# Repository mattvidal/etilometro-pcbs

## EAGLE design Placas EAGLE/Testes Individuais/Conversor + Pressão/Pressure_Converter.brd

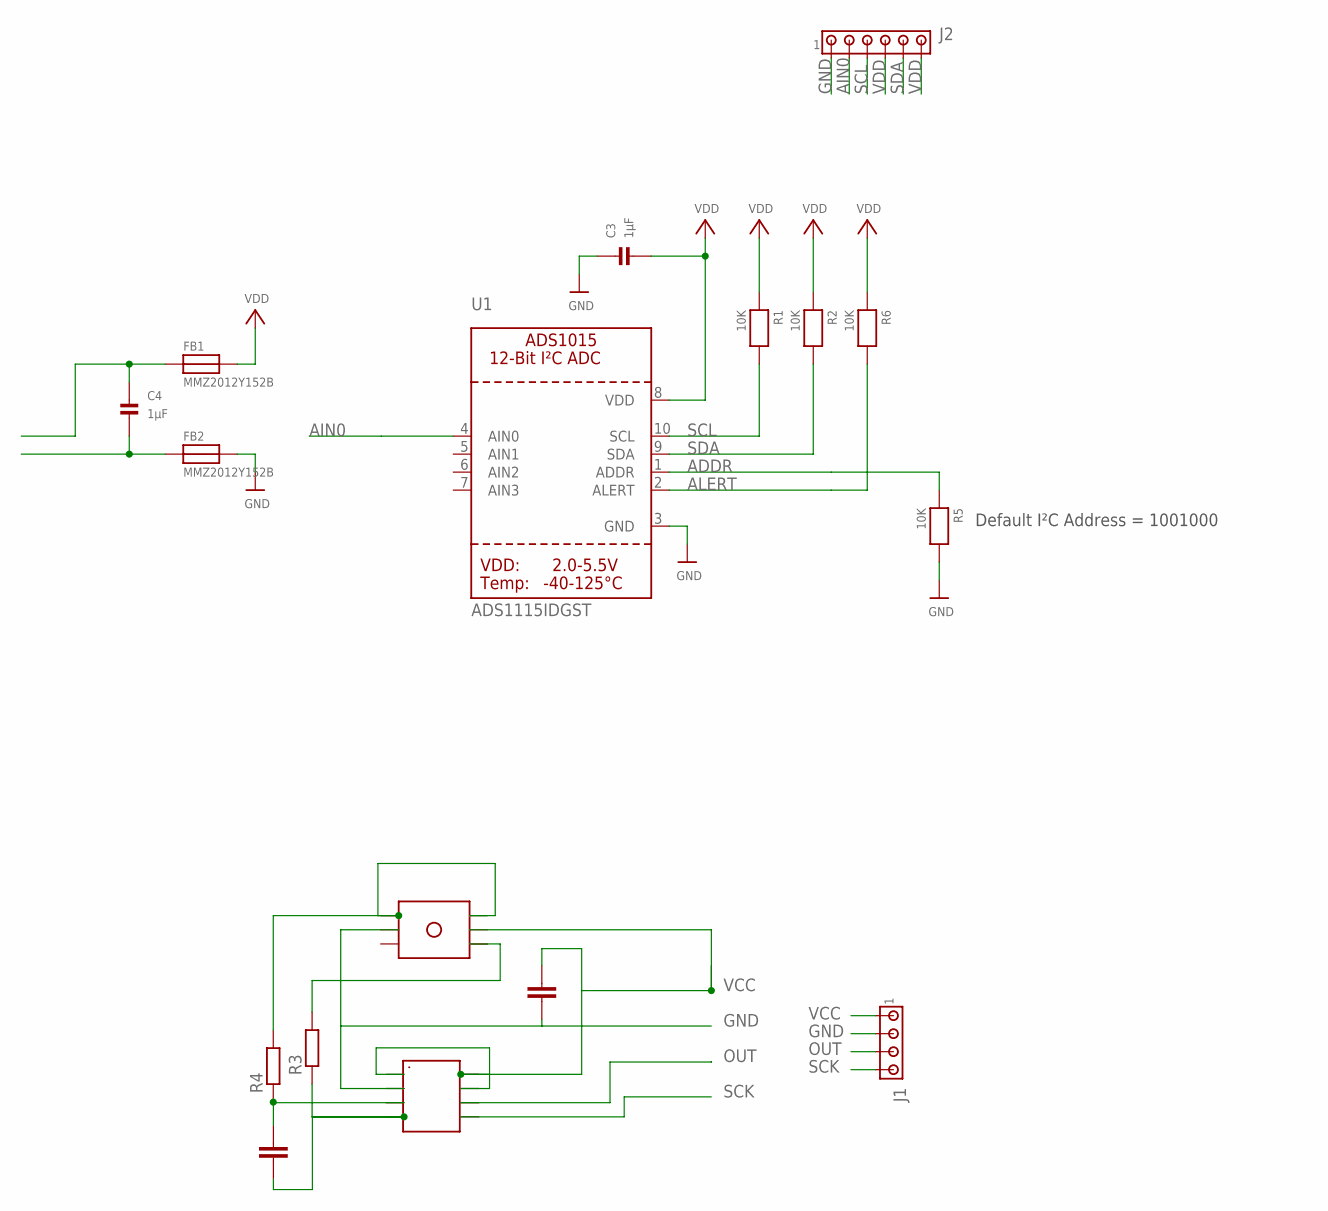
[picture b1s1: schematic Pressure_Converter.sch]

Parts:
C1, C2: 100n; C0805
C3, C4: 1µF; 0805
FB1, FB2: MMZ2012Y152B; 0805
J1: MTA04-100; 10X04MTA
J2: MTA06-156; 1X6MTA
R1, R2, R5, R6: 10K; 0805
R3, R4: R-EU_R0805; R0805
U1: ADS1115IDGST; MSOP10
U$1: HX710B
U$2: PRESSURE

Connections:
ADDR: R5.1, U1.1 (ADDR)
AIN0: J2.2, U1.4 (AIN0)
ALERT: R6.2, U1.2 (ALERT)
GND: C1.2, C3.1, FB2.2, J1.2, J2.1, R5.2, U1.3 (GND), U$1.AGND, U$2.2
unnamed: C2.2, R4.1, U$1.INN
unnamed: C2.1, R3.1, U$1.INP
unnamed: R3.2, U$2.4
unnamed: R4.2, U$2.1, U$2.6
unnamed: C4.2, FB2.1
unnamed: C4.1, FB1.1
OUT: J1.3, U$1.DOUT
SCK: J1.4, U$1.SCK
SCL: J2.3, R1.2, U1.10 (SCL)
SDA: J2.5, R2.2, U1.9 (SDA)
VCC: C1.1, J1.1, U$1.AVDD, U$1.DVDD, U$1.VREF, U$2.5
VDD: C3.2, FB1.2, J2.4, J2.6, R1.1, R2.1, R6.1, U1.8 (VDD)

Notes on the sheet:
Default I²C Address = 1001000

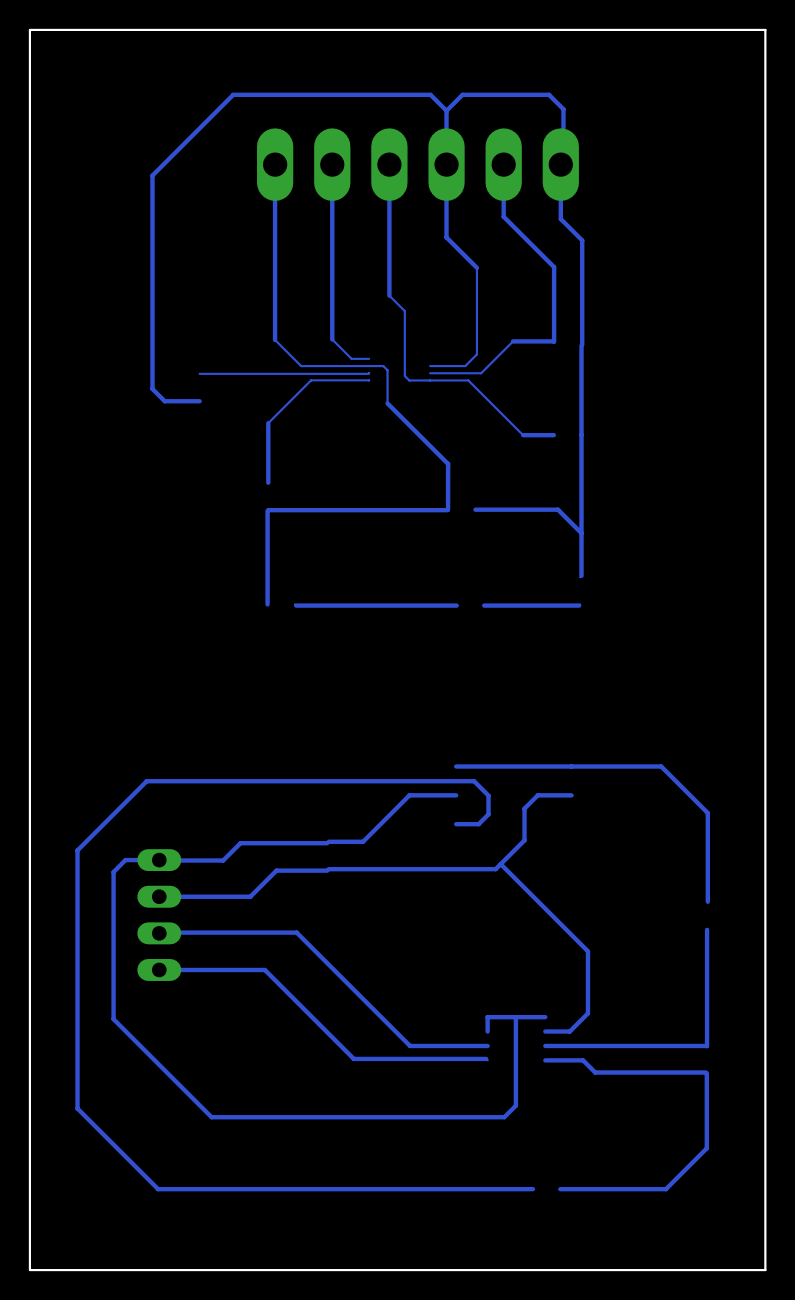
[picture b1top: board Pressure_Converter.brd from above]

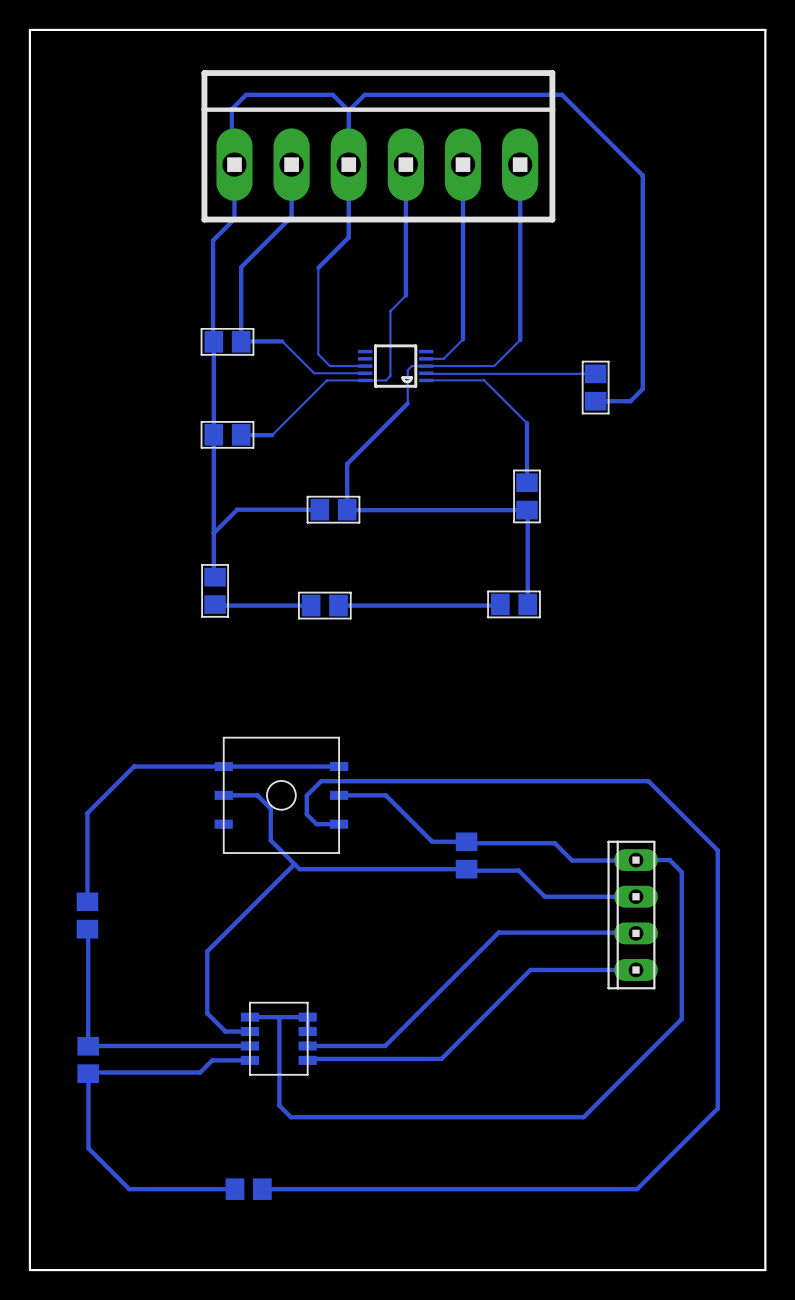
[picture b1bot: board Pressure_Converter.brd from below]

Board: 2 copper layers, 51.0 x 86.0 mm, 17 parts (17 on the bottom side), 16 nets.

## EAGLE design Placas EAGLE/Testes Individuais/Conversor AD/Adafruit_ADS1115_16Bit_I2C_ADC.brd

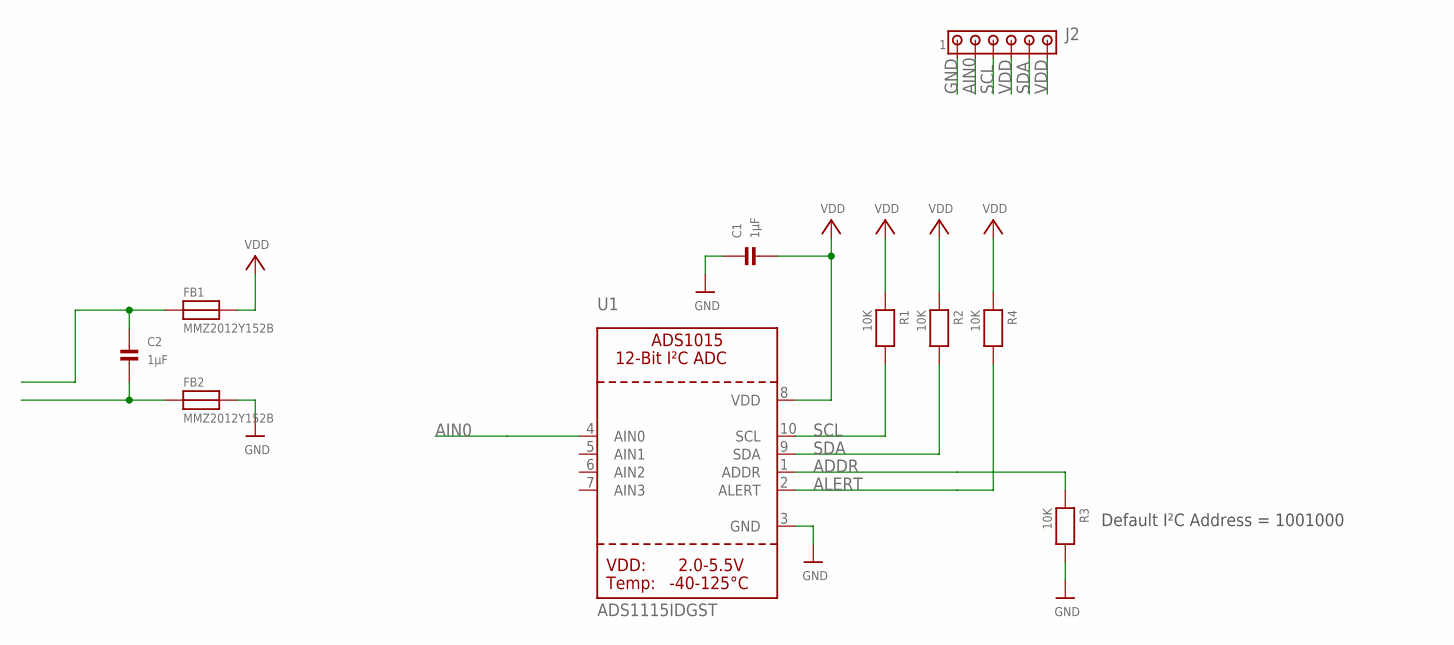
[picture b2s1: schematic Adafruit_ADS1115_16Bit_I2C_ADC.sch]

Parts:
C1, C2: 1µF; 0805
FB1, FB2: MMZ2012Y152B; 0805
J2: MTA06-156; 1X6MTA
R1, R2, R3, R4: 10K; 0805
U1: ADS1115IDGST; MSOP10

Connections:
ADDR: R3.1, U1.1 (ADDR)
AIN0: J2.2, U1.4 (AIN0)
ALERT: R4.2, U1.2 (ALERT)
GND: C1.1, FB2.2, J2.1, R3.2, U1.3 (GND)
unnamed: C2.1, FB1.1
unnamed: C2.2, FB2.1
SCL: J2.3, R1.2, U1.10 (SCL)
SDA: J2.5, R2.2, U1.9 (SDA)
VDD: C1.2, FB1.2, J2.4, J2.6, R1.1, R2.1, R4.1, U1.8 (VDD)

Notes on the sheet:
Default I²C Address = 1001000

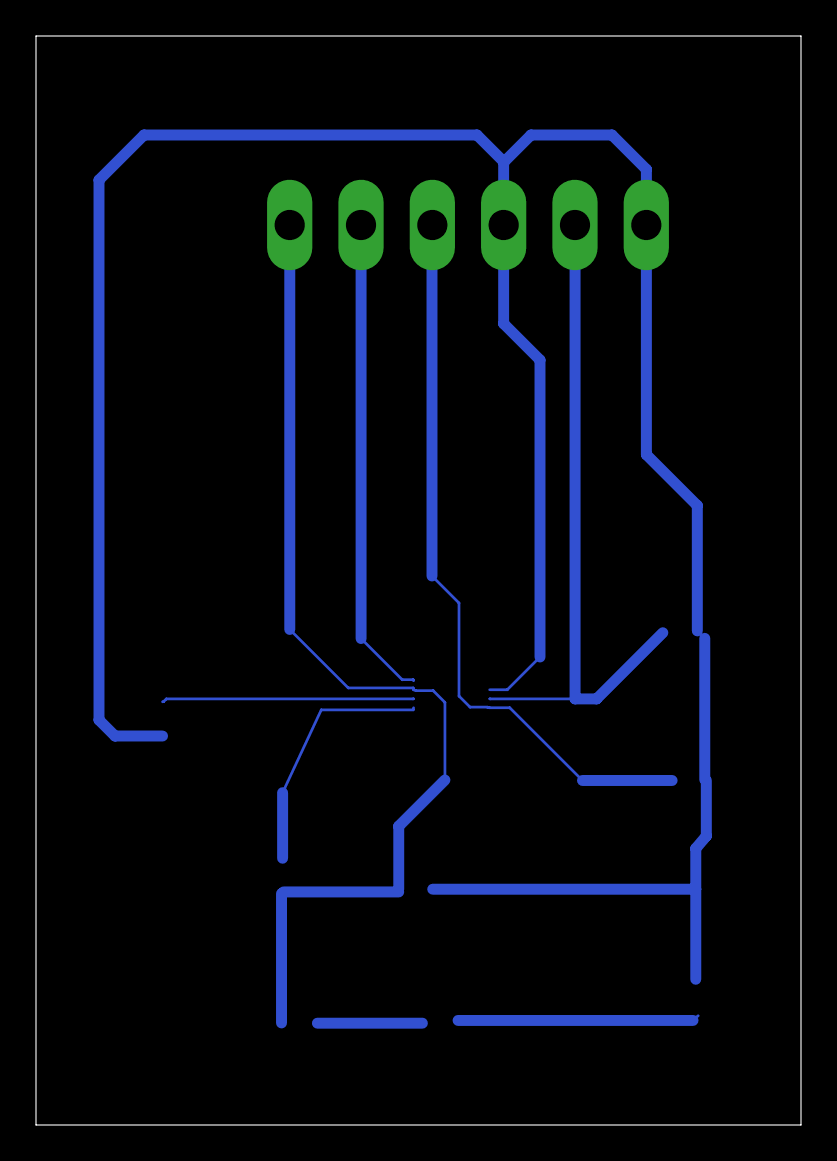
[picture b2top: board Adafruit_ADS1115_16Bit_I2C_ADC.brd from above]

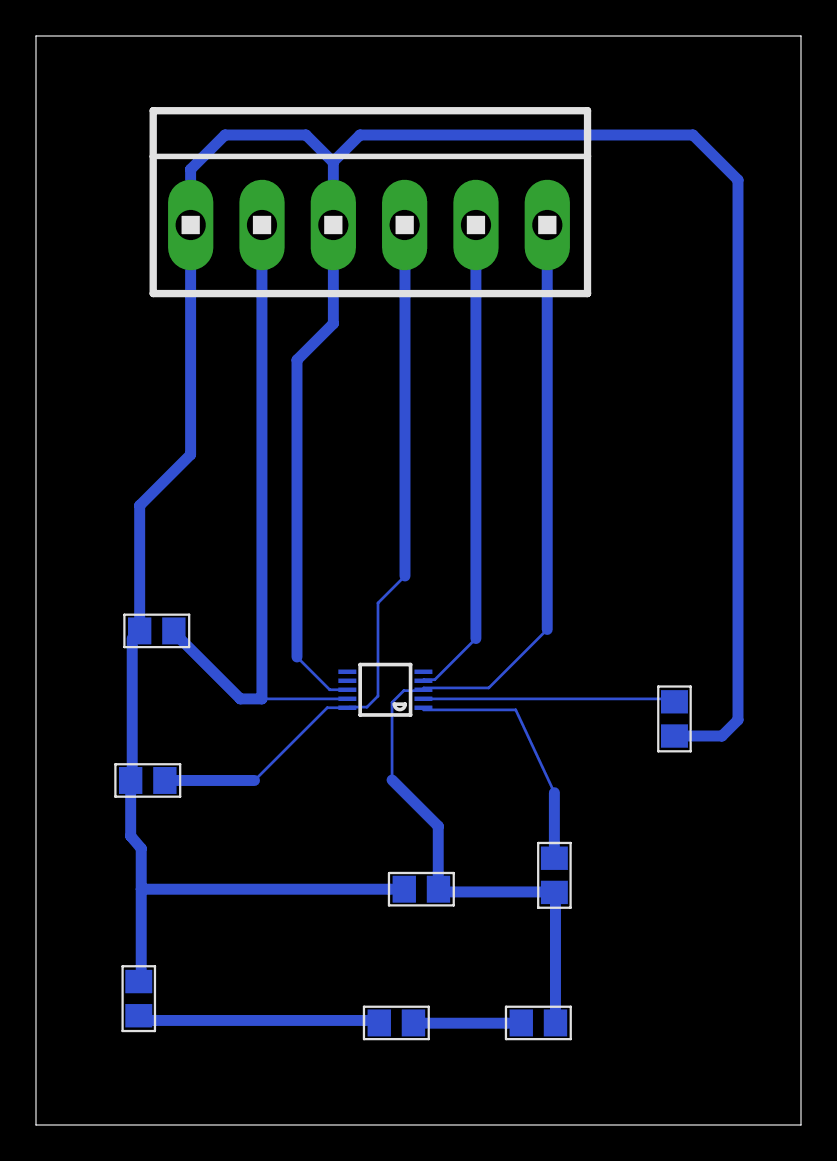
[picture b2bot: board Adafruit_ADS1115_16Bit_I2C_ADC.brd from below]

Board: 2 copper layers, 42.5 x 60.5 mm, 10 parts (10 on the bottom side), 9 nets.

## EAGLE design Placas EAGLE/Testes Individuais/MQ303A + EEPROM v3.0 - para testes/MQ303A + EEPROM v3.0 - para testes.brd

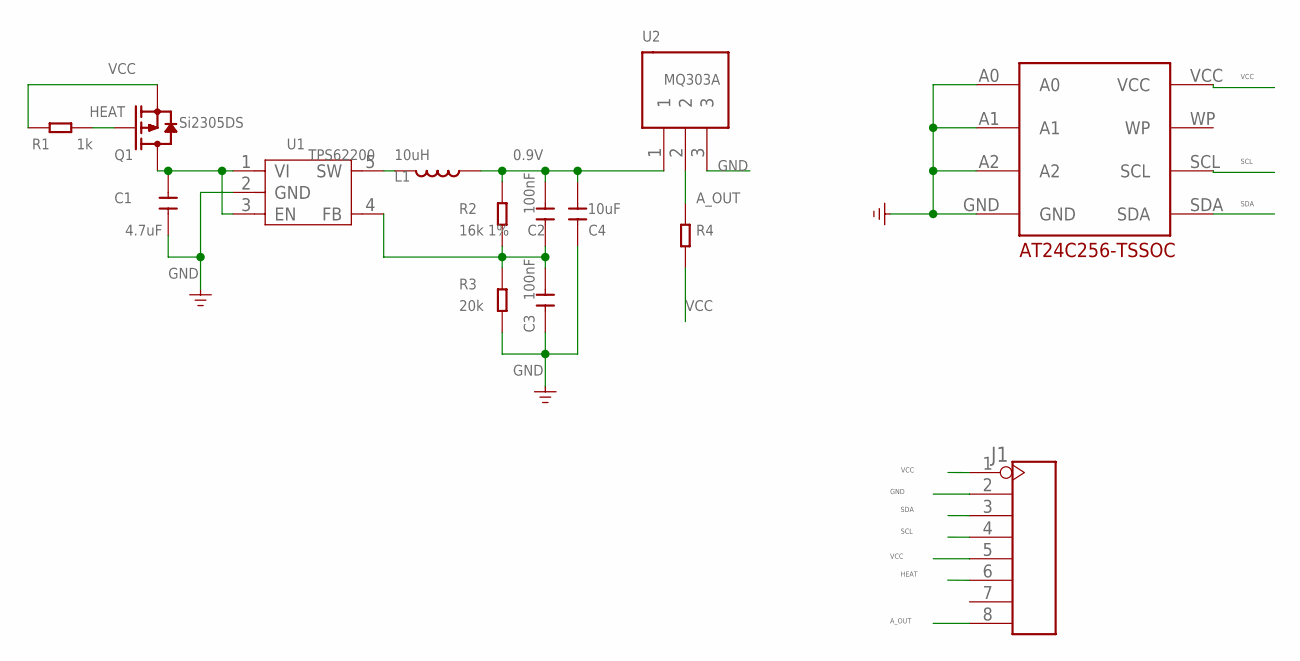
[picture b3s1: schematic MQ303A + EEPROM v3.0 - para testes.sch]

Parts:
C1: 4.7uF; C0805
C2, C3: 100nF; C0603
C4: 10uF; C0805
J1: HEADER-8P-2.54; 8P-2.54
L1: 10uH; PIO73
Q1: Si2305DS; SOT23
R1: 1k; R0603
R2: 16k 1%; R0603
R3: 20k; R0603
R4: R-0603; R0603
U1: TPS62200; SOT23-5
U2: MQ303A
U$1: DECADE-AT24C256-10TI-2.7; DECADE-AT24CXX

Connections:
0.9V: C2.2, C4.2, L1.2, R2.1, U2.1
A_OUT: J1.8, R4.1, U2.2
GND: C1.2, C3.1, C4.1, J1.2, R3.2, U1.2 (GND), U2.3, U$1.A0, U$1.A1, U$1.A2, U$1.GND
HEAT: J1.6, Q1.1 (G), R1.1
unnamed: C1.1, Q1.3 (D), U1.1 (VI), U1.3 (EN)
unnamed: L1.1, U1.5 (SW)
unnamed: C2.1, C3.2, R2.2, R3.1, U1.4 (FB)
SCL: J1.4, U$1.SCL
SDA: J1.3, U$1.SDA
VCC: J1.1, J1.5, Q1.2 (S), R1.2, R4.2, U$1.VCC

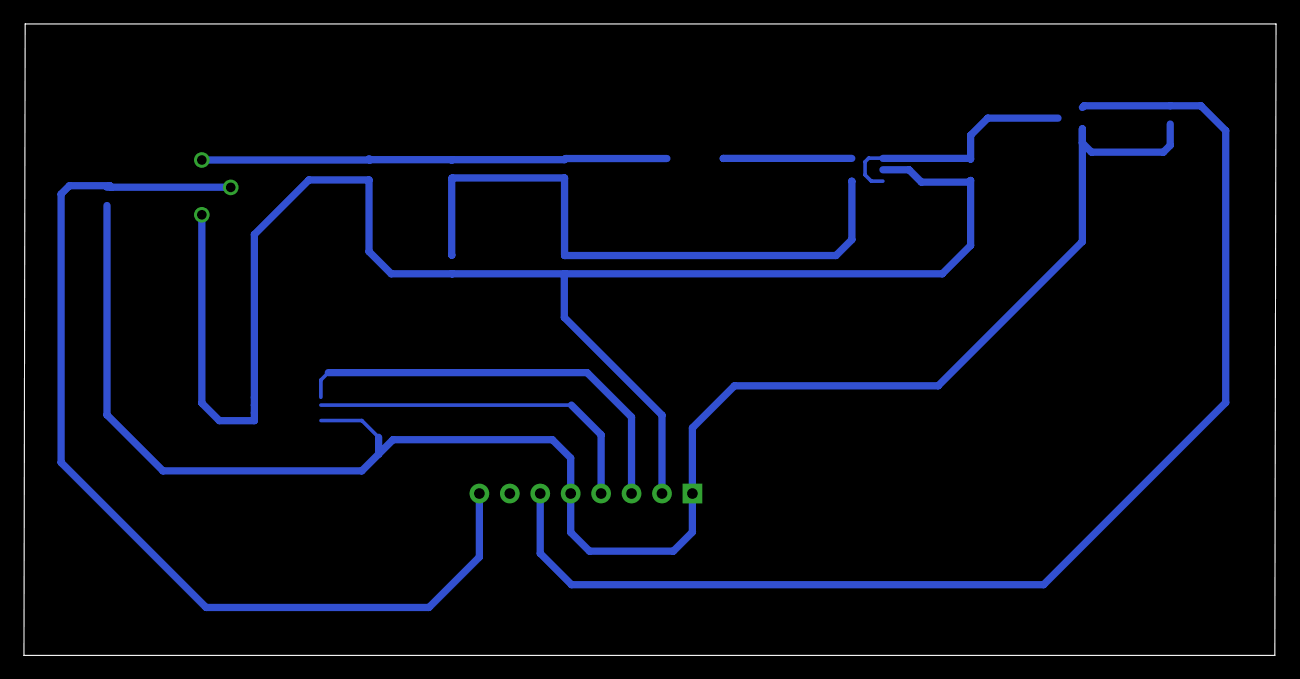
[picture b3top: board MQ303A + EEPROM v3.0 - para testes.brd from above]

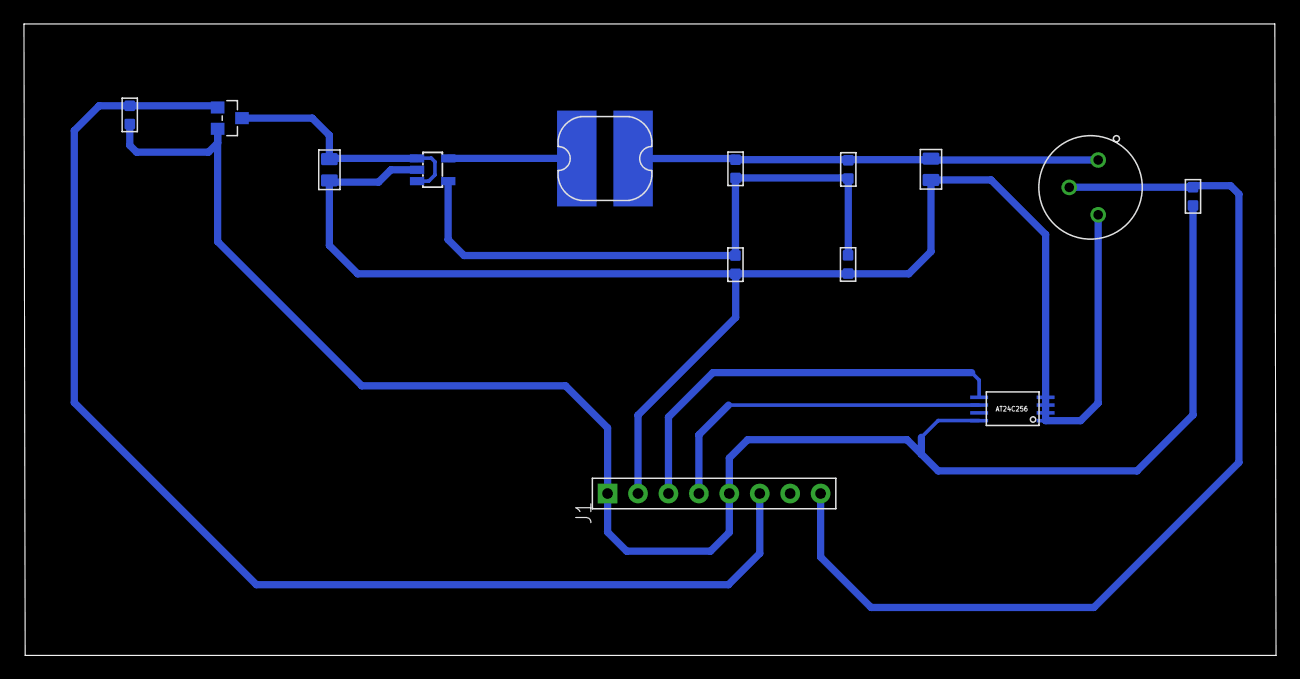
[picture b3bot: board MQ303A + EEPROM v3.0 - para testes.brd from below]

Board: 2 copper layers, 104.5 x 52.7 mm, 14 parts (14 on the bottom side), 10 nets.

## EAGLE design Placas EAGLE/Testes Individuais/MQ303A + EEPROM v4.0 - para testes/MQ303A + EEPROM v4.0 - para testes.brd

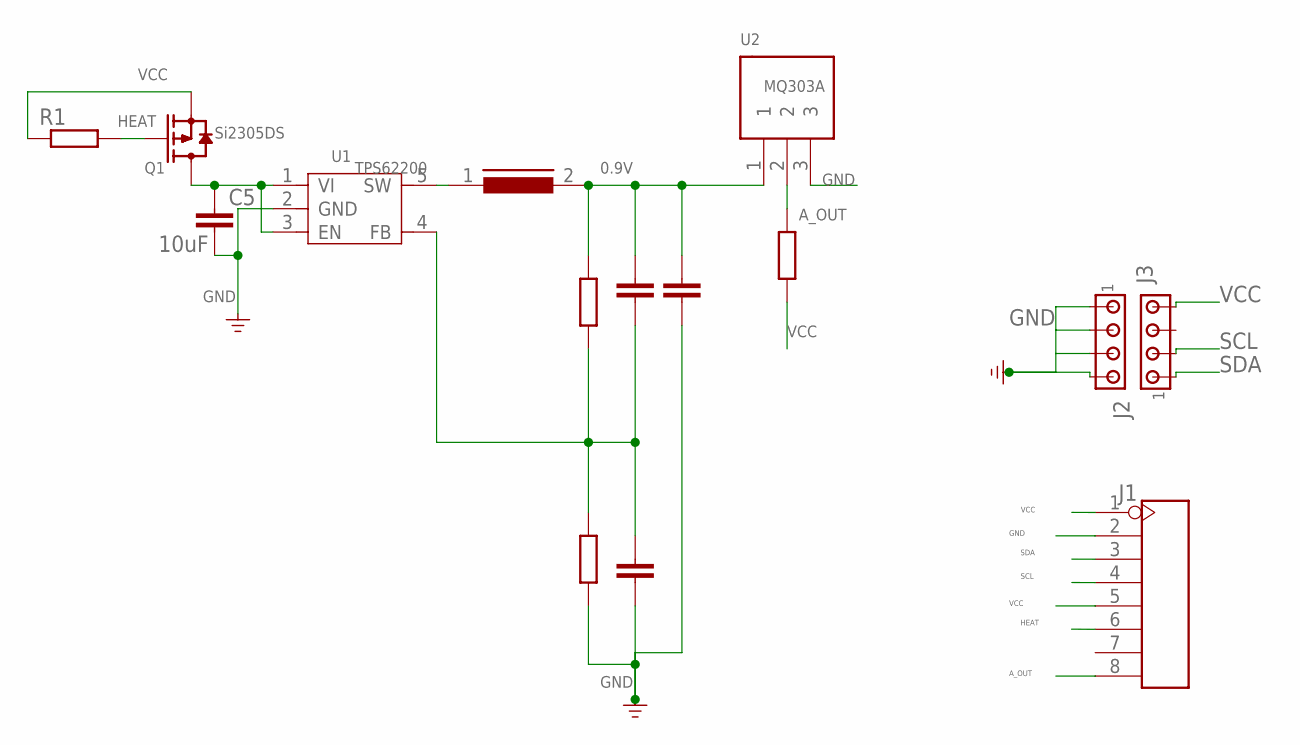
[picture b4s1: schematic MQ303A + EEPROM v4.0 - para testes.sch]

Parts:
C1, C2, C3, C5: 10uF; C050-025X075
J1: HEADER-8P-2.54; 8P-2.54
J2, J3: MTA04-100; 10X04MTA
L2: MMICC7
Q1: Si2305DS; SOT23
R1, R2, R3, R5: R-EU_0207/10; 0207/10
U1: TPS62200; SOT23-5
U2: MQ303A

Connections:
0.9V: C1.1, C3.1, L2.2, R5.2, U2.1
A_OUT: J1.8, R3.2, U2.2
GND: C2.2, C3.2, C5.2, J1.2, J2.1, J2.2, J2.3, J2.4, R2.1, U1.2 (GND), U2.3
HEAT: J1.6, Q1.1 (G), R1.2
unnamed: C5.1, Q1.3 (D), U1.1 (VI), U1.3 (EN)
unnamed: L2.1, U1.5 (SW)
unnamed: C1.2, C2.1, R2.2, R5.1, U1.4 (FB)
SCL: J1.4, J3.2
SDA: J1.3, J3.1
VCC: J1.1, J1.5, J3.4, Q1.2 (S), R1.1, R3.1

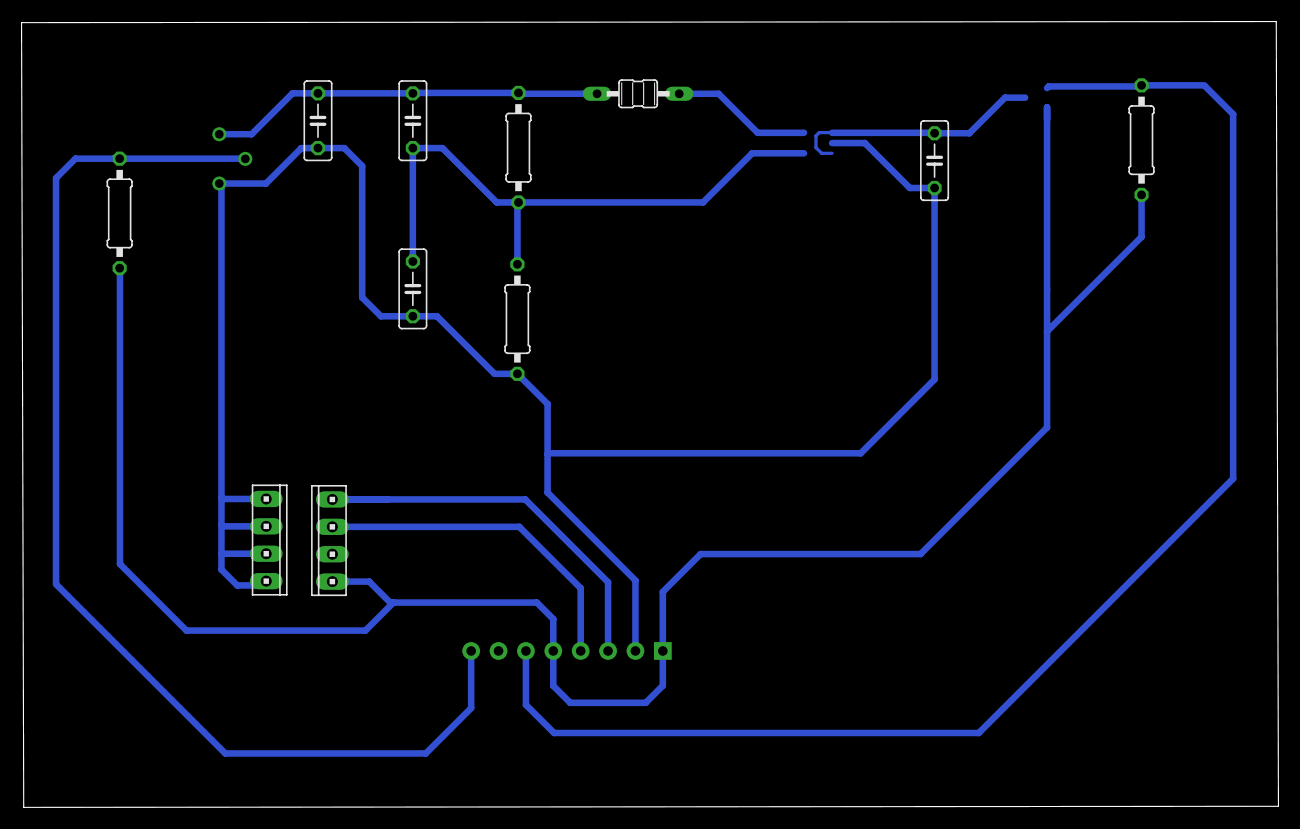
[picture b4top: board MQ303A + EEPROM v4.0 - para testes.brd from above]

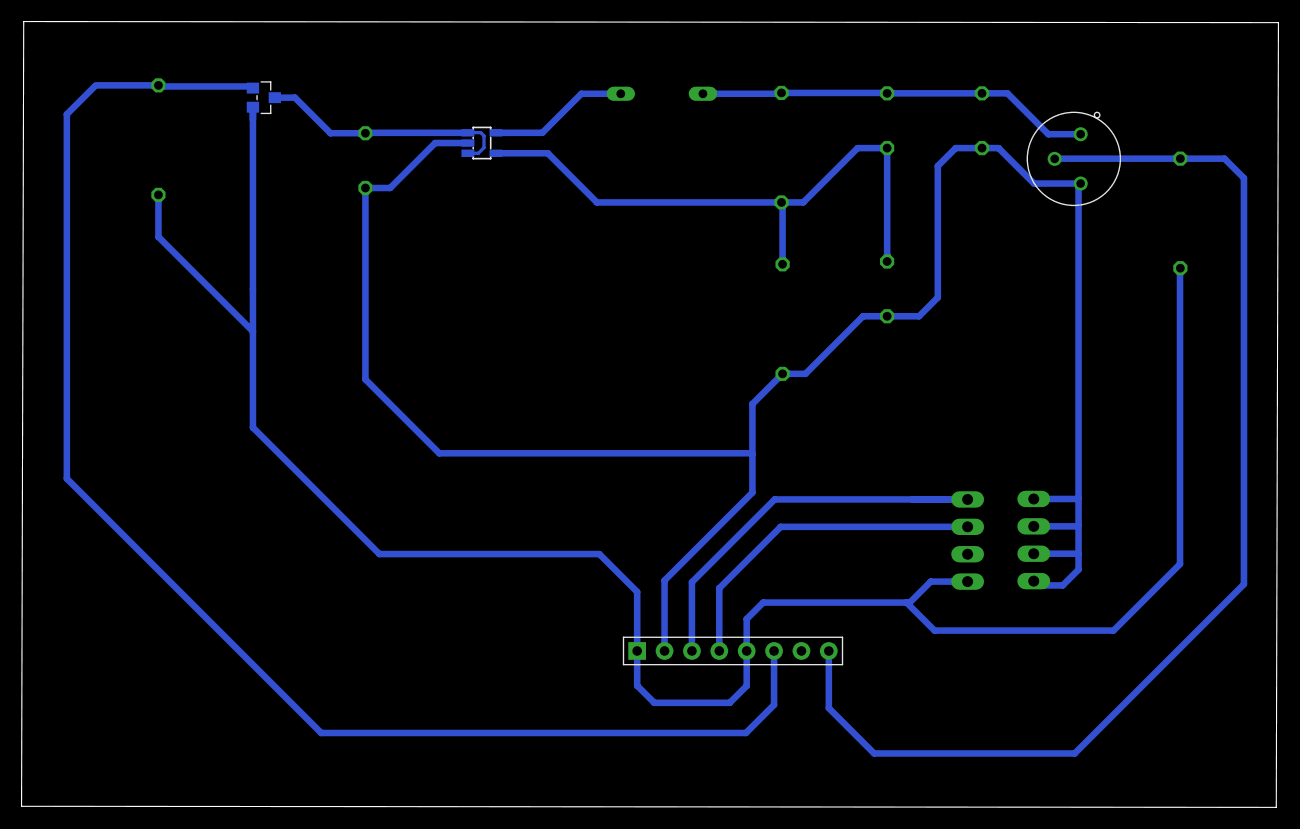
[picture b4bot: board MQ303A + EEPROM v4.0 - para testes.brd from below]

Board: 2 copper layers, 116.6 x 72.9 mm, 15 parts (4 on the bottom side), 10 nets.

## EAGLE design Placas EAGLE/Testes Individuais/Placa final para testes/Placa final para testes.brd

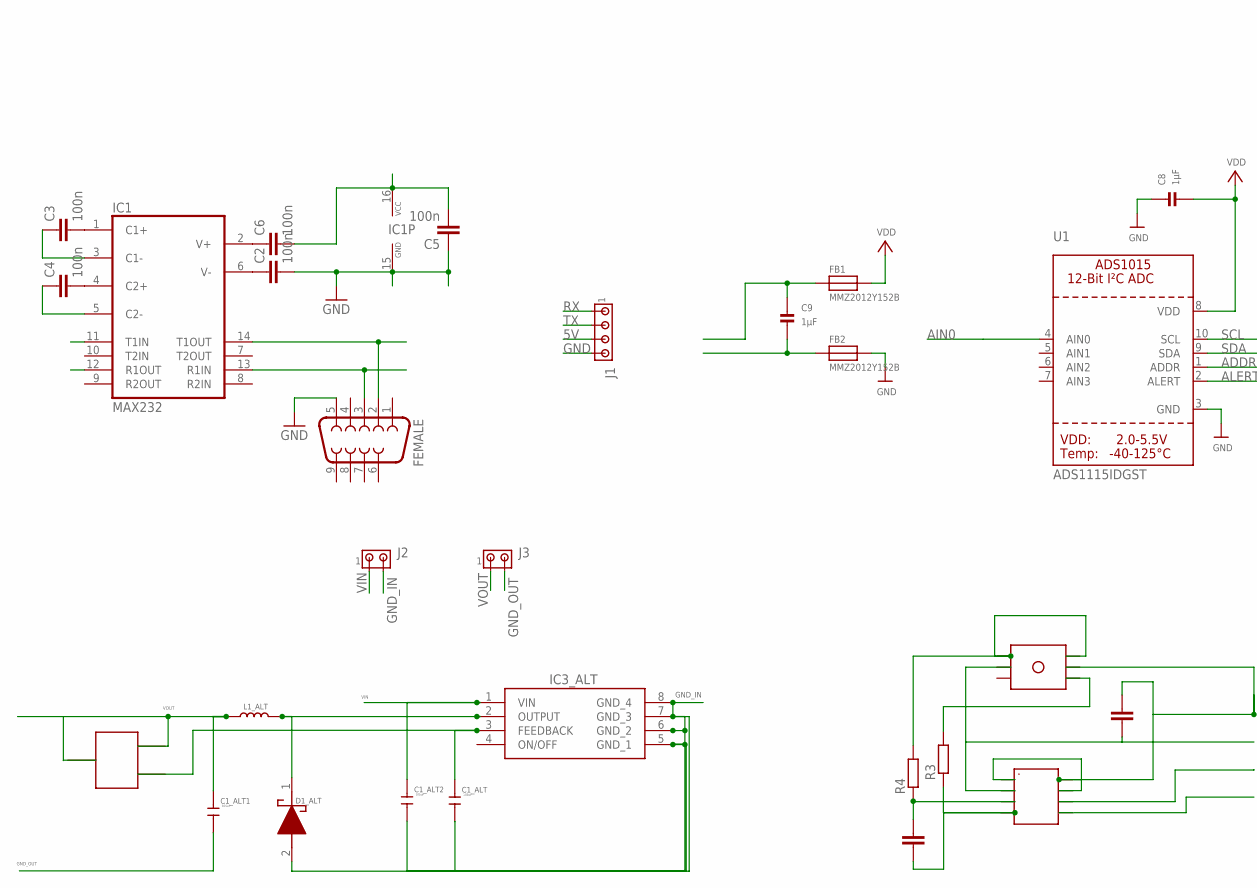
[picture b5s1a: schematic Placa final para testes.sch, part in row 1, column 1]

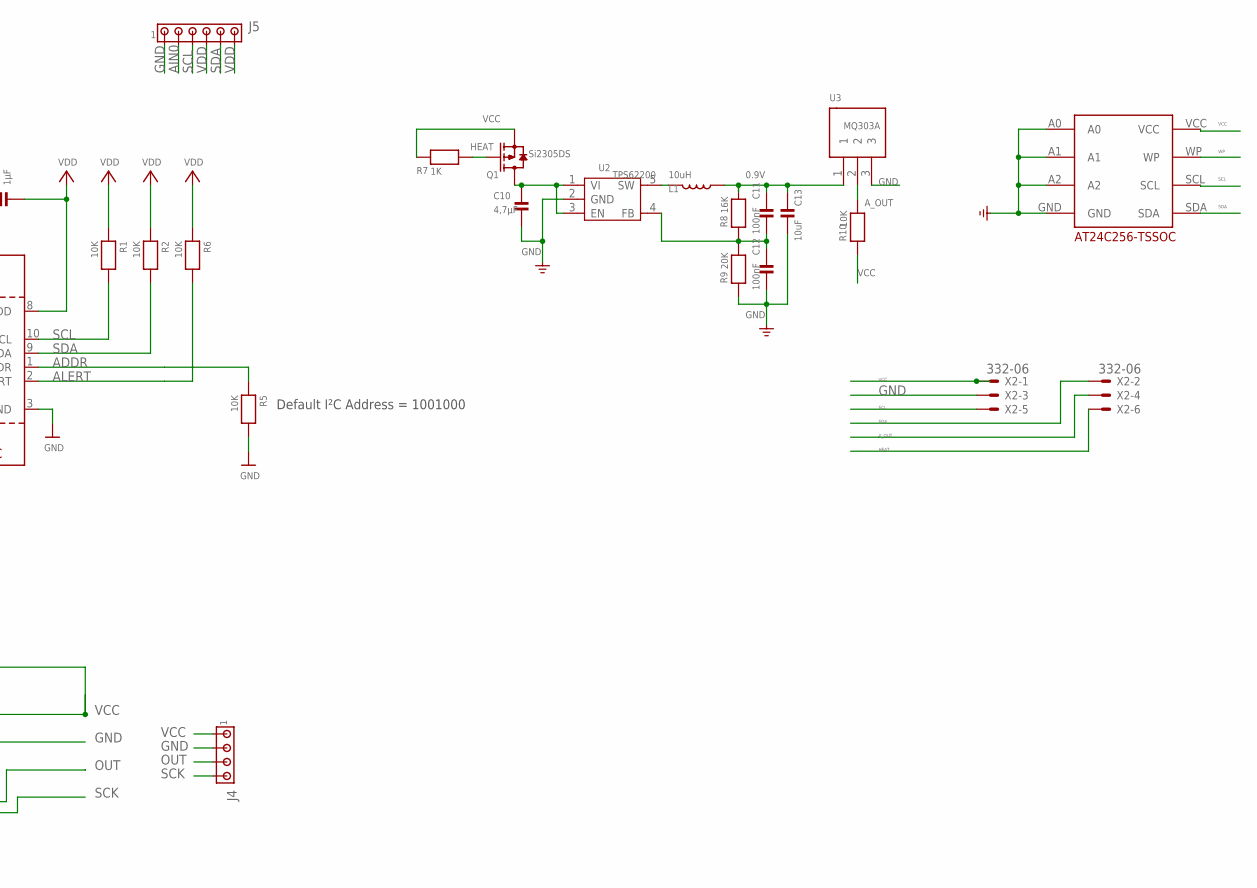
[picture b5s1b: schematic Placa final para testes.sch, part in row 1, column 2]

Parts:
C1, C2, C3, C4, C5, C6, C7: 100n; C0805
C1_ALT, C1_ALT1, C1_ALT2: 105uF; C0805
C8, C9: 1µF; 0805
C10: 4,7µF; 0805
C11, C12: 100nF; 0805
C13: 10uF; 0805
D1_ALT: 1N5819HW1-7-F; SODFL3518X115N
FB1, FB2: MMZ2012Y152B; 0805
FEMALE: F09H
IC1: MAX232; SO16
IC3_ALT: XL1509-3.3E1; SOIC127P600X175-8N
J1: MTA04-156; 1X4MTA
J2, J3: MTA02-156; 1X2MTA
J4: MTA04-100; 10X04MTA
J5: MTA06-156; 1X6MTA
L1: 10uH; PIO73
L1_ALT: 47uH; PIO73
Q1: Si2305DS; SOT23
R1, R2, R5, R6, R10: 10K; 0805
R3, R4: R-EU_R0805; R0805
R7: 1K; 0805
R8: 16K; 0805
R9: 20K; 0805
U1: ADS1115IDGST; MSOP10
U2: TPS62200; SOT23-5
U3: MQ303A
U$1: TRIMPOT
U$2: HX710B
U$3: PRESSURE
U$15: DECADE-AT24C256-10TI-2.7; DECADE-AT24CXX
X2: 332-06

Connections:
0.9V: C11.1, C13.1, L1.2, R8.2, U3.1
5V: C5.2, C6.2, IC1.16 (VCC), J1.3
ADDR: R5.1, U1.1 (ADDR)
AIN0: J5.2, U1.4 (AIN0)
ALERT: R6.2, U1.2 (ALERT)
A_OUT: R10.2, U3.2, X2.4
GND: C2.2, C5.1, C7.2, C8.1, C10.2, C12.2, C13.2, FB2.2, FEMALE.5, IC1.15 (GND), J1.4, J4.2, J5.1, R5.2, R9.1, U1.3 (GND), U2.2 (GND), U3.3, U$2.AGND, U$3.2, U$15.A0, U$15.A1, U$15.A2, U$15.GND, X2.3
GND_IN: C1_ALT.1, C1_ALT2.1, D1_ALT.2 (A), IC3_ALT.5 (GND_1), IC3_ALT.6 (GND_2), IC3_ALT.7 (GND_3), IC3_ALT.8 (GND_4), J2.2
GND_OUT: C1_ALT1.1, J3.2
HEAT: Q1.1 (G), R7.2, X2.6
unnamed: C1.2, R4.1, U$2.INN
unnamed: C1.1, R3.1, U$2.INP
unnamed: D1_ALT.1 (K), IC3_ALT.2 (OUTPUT), L1_ALT.1
unnamed: R4.2, U$3.1, U$3.6
unnamed: R3.2, U$3.4
unnamed: C9.2, FB2.1
unnamed: C9.1, FB1.1
unnamed: C1_ALT.2, IC3_ALT.3 (FEEDBACK), U$1.OUT
unnamed: C10.1, Q1.3 (D), U2.1 (VI), U2.3 (EN)
unnamed: C3.2, IC1.1 (C1+)
unnamed: L1.1, U2.5 (SW)
unnamed: C4.2, IC1.4 (C2+)
unnamed: C3.1, IC1.3 (C1-)
unnamed: C4.1, IC1.5 (C2-)
unnamed: C6.1, IC1.2 (V+)
unnamed: C2.1, IC1.6 (V-)
unnamed: C11.2, C12.1, R8.1, R9.2, U2.4 (FB)
unnamed: FEMALE.2, IC1.14 (T1OUT)
unnamed: FEMALE.3, IC1.13 (R1IN)
OUT: J4.3, U$2.DOUT
RX: IC1.12 (R1OUT), J1.1
SCK: J4.4, U$2.SCK
SCL: J5.3, R1.2, U1.10 (SCL), U$15.SCL, X2.5
SDA: J5.5, R2.2, U1.9 (SDA), U$15.SDA, X2.2
TX: IC1.11 (T1IN), J1.2
VCC: C7.1, J4.1, Q1.2 (S), R7.1, R10.1, U$2.AVDD, U$2.DVDD, U$2.VREF, U$3.5, U$15.VCC, X2.1
VDD: C8.2, FB1.2, J5.4, J5.6, R1.1, R2.1, R6.1, U1.8 (VDD)
VIN: C1_ALT2.2, IC3_ALT.1 (VIN), J2.1
VOUT: C1_ALT1.2, J3.1, L1_ALT.2, U$1.VCC1, U$1.VCC2
WP: U$15.WP

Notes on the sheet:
Default I²C Address = 1001000

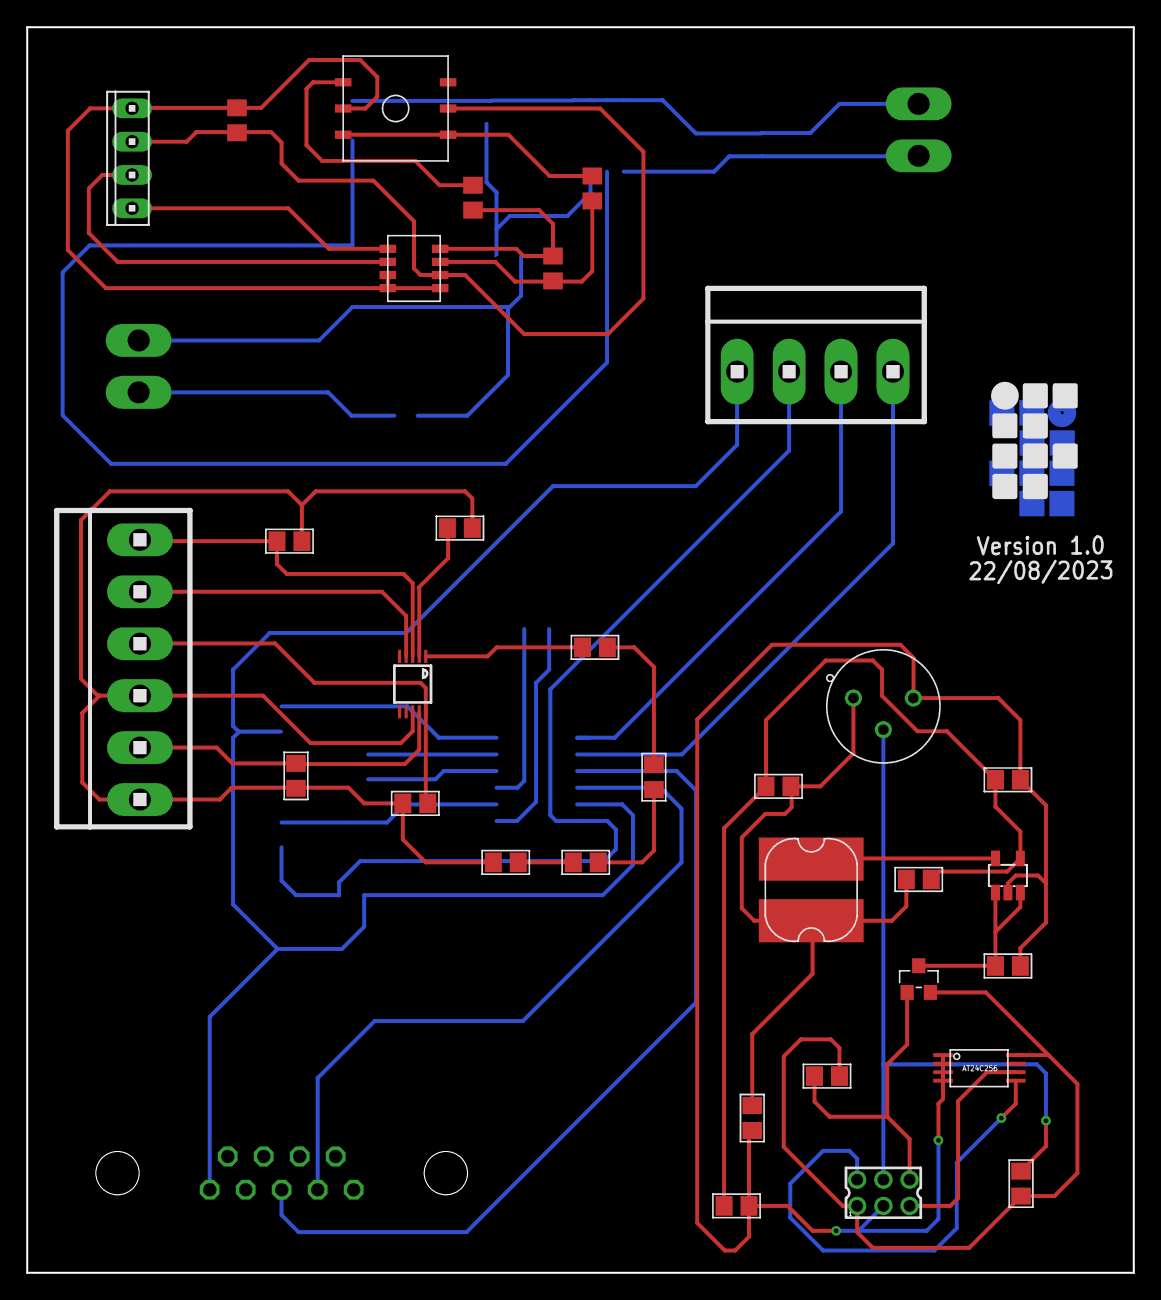
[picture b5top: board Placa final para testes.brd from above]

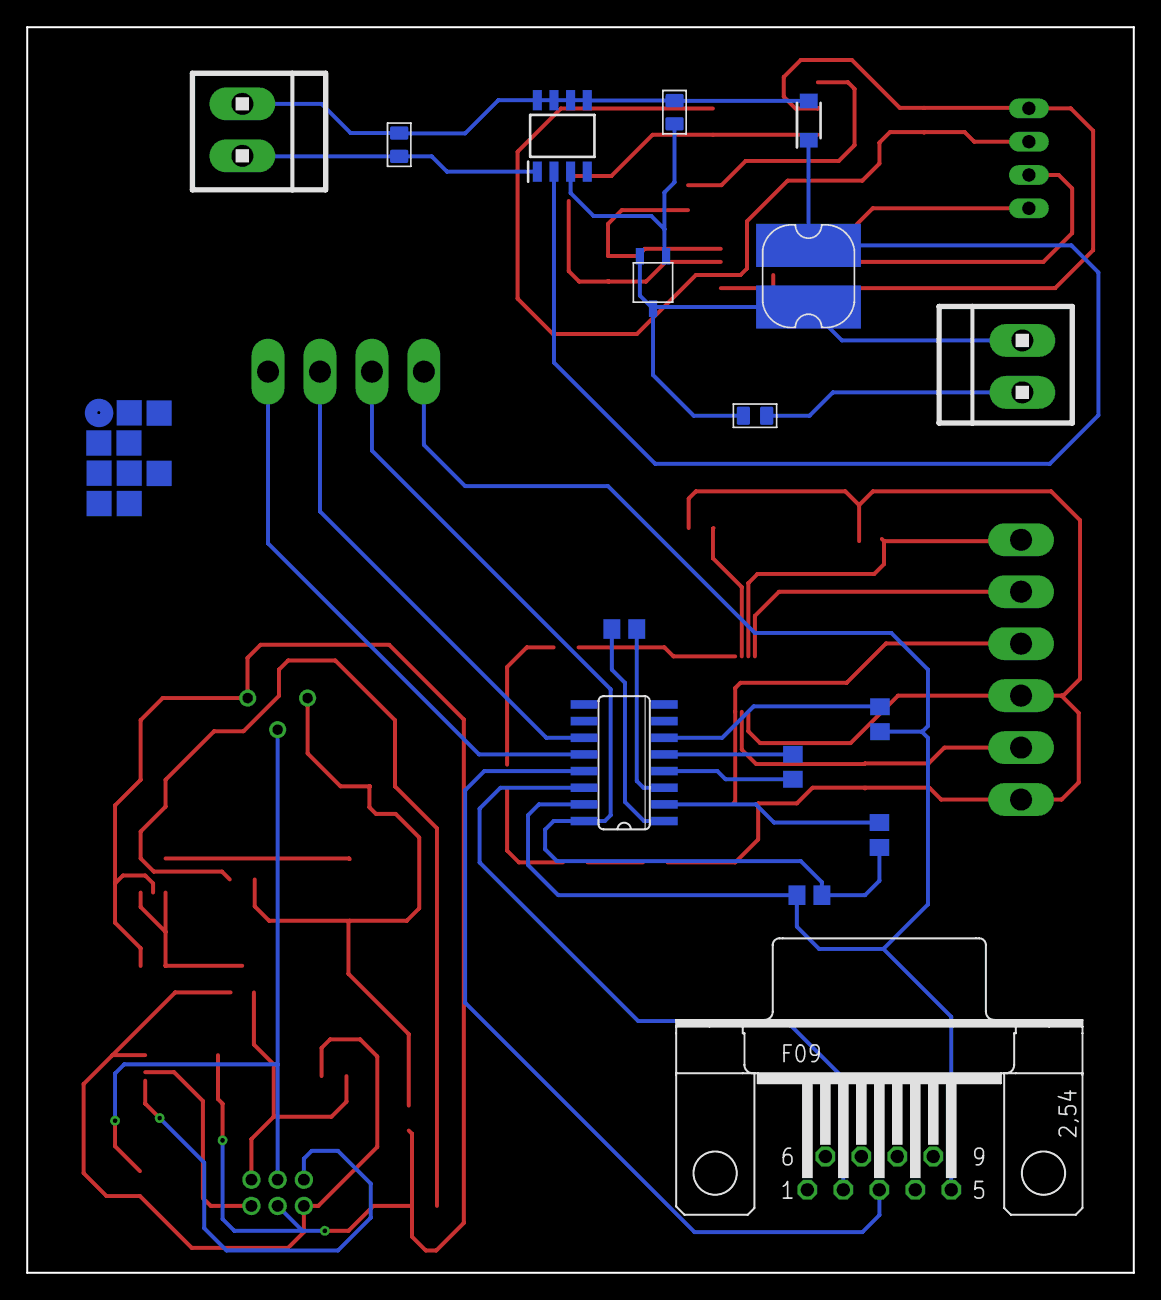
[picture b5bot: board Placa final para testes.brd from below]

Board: 2 copper layers, 84.4 x 95.0 mm, 48 parts (16 on the bottom side), 39 nets.

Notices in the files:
parts and their libraries:
DECADE-libraries20151104: Licensing: Creative Commons ShareAlike 4.0 International - https://creativecommons.org/licenses/by-sa/4.0
